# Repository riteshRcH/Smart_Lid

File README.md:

# Smart Lid 2018

* Components used: AVR, Ultrasonic Sensor with PWM output, HC06 Bluetooth
* This project aims to monitor water tank level and accordingly turn water pump on/off w.r.t user defined threshold %
* Current level can be monitored & accessed using companion Android app

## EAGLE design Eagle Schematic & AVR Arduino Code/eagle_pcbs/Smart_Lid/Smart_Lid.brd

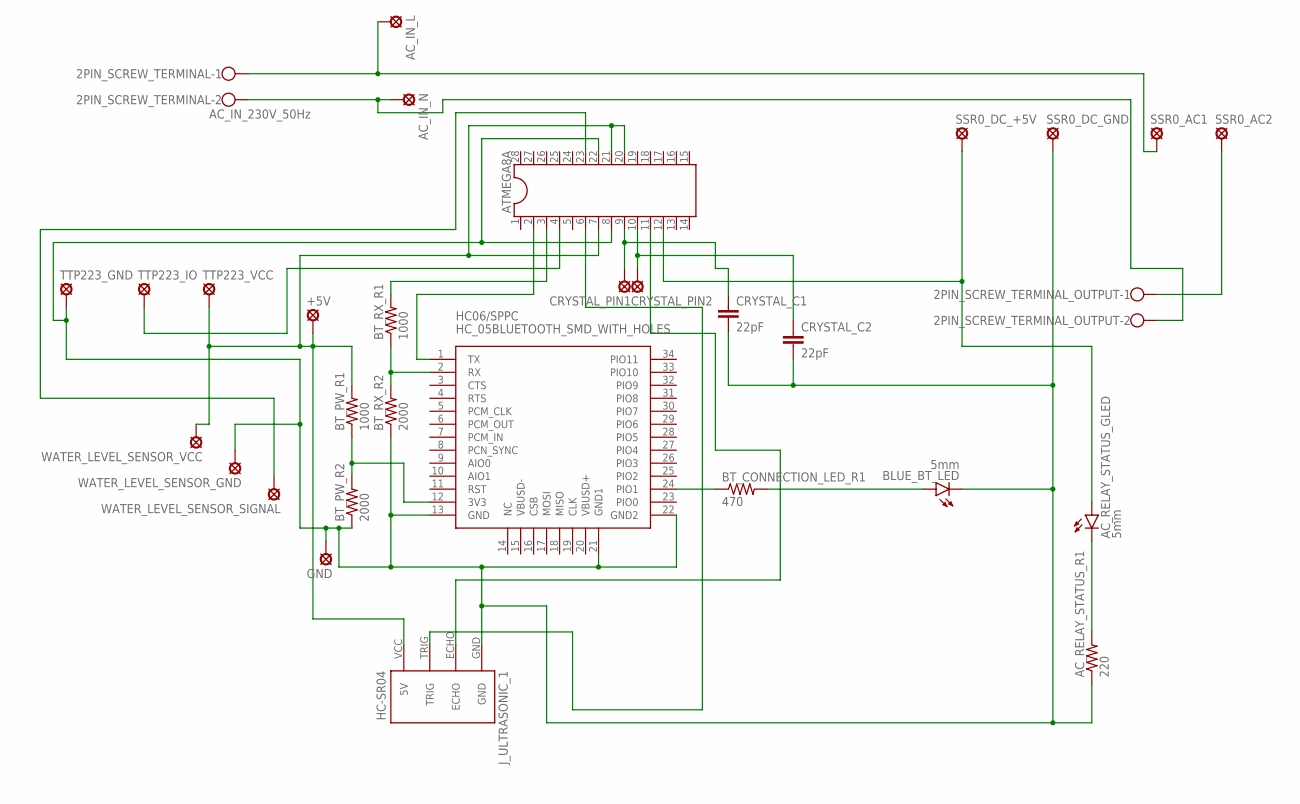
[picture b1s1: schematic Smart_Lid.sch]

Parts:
2PIN_SCREW_TERMINAL: AC_IN_230V_50Hz; W237-102
2PIN_SCREW_TERMINAL_OUTPUT: W237-102
+5V: LSP10
AC_IN_L: LSP10
AC_IN_N: LSP10
AC_RELAY_STATUS_GLED: 5mm; LED5MM
AC_RELAY_STATUS_R1: 220; 1206
ATMEGA8A: DIL28DIL28-3_MODIFIED; DIL28-3
BLUE_BT_LED: 5mm; LED5MM
BT_CONNECTION_LED_R1: 470; 1206
BT_PW_R1: 1000; 1206
BT_PW_R2: 2000; 1206
BT_RX_R1: 1000; 1206
BT_RX_R2: 2000; 1206
CRYSTAL_C1, CRYSTAL_C2: 22pF; 1206
CRYSTAL_PIN1, CRYSTAL_PIN2: LSP10
GND: LSP10
HC06/SPPC: HC_05BLUETOOTH_SMD_WITH_HOLES; BLUETOOTH_SMD
J_ULTRASONIC_1: HC-SR04; HC-SR04_FOOTPRINT
SSR0_AC1, SSR0_AC2, SSR0_DC_+5V, SSR0_DC_GND: LSP10
TTP223_GND, TTP223_IO, TTP223_VCC: LSP10
WATER_LEVEL_SENSOR_GND: LSP10
WATER_LEVEL_SENSOR_SIGNAL: LSP10
WATER_LEVEL_SENSOR_VCC: LSP10

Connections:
unnamed: ATMEGA8A.2, HC06/SPPC.1 (TX)
unnamed: 2PIN_SCREW_TERMINAL.1, AC_IN_L.MP, SSR0_AC1.MP
unnamed: 2PIN_SCREW_TERMINAL_OUTPUT.1, SSR0_AC2.MP
unnamed: BT_CONNECTION_LED_R1.1, HC06/SPPC.24 (PIO1)
unnamed: BLUE_BT_LED.A, BT_CONNECTION_LED_R1.2
unnamed: BT_RX_R1.1, BT_RX_R2.2, HC06/SPPC.2 (RX)
unnamed: AC_RELAY_STATUS_R1.1, ATMEGA8A.8, ATMEGA8A.22, BLUE_BT_LED.K (C), BT_PW_R2.1, BT_RX_R2.1, CRYSTAL_C1.2, CRYSTAL_C2.2, GND.MP, HC06/SPPC.13 (GND), HC06/SPPC.21 (GND1), HC06/SPPC.22 (GND2), J_ULTRASONIC_1.GND, SSR0_DC_GND.MP, TTP223_GND.MP, WATER_LEVEL_SENSOR_GND.MP
unnamed: ATMEGA8A.23, WATER_LEVEL_SENSOR_SIGNAL.MP
unnamed: ATMEGA8A.3, BT_RX_R1.2
unnamed: 2PIN_SCREW_TERMINAL.2, 2PIN_SCREW_TERMINAL_OUTPUT.2, AC_IN_N.MP
unnamed: ATMEGA8A.4, TTP223_IO.MP
unnamed: +5V.MP, ATMEGA8A.7, ATMEGA8A.20, ATMEGA8A.21, BT_PW_R1.2, J_ULTRASONIC_1.VCC (5V), TTP223_VCC.MP, WATER_LEVEL_SENSOR_VCC.MP
unnamed: ATMEGA8A.6, J_ULTRASONIC_1.TRIG
unnamed: ATMEGA8A.9, CRYSTAL_C1.1, CRYSTAL_PIN1.MP
unnamed: ATMEGA8A.10, CRYSTAL_C2.1, CRYSTAL_PIN2.MP
unnamed: AC_RELAY_STATUS_GLED.K (C), AC_RELAY_STATUS_R1.2
unnamed: AC_RELAY_STATUS_GLED.A, ATMEGA8A.12, SSR0_DC_+5V.MP
unnamed: ATMEGA8A.11, J_ULTRASONIC_1.ECHO
unnamed: BT_PW_R1.1, BT_PW_R2.2, HC06/SPPC.12 (3V3)

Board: 2 copper layers, 31 parts (0 on the bottom side), 19 nets, no tracks yet.

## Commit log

2019-12-21 Smart Lid Eagle Schematics, Arduino Code & Android App
2019-12-22 added screenshots

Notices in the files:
parts and their libraries:
SparkFun-LED: Licensing: Creative Commons ShareAlike 4.0 International - https://creativecommons.org/licenses/by-sa/4.0
